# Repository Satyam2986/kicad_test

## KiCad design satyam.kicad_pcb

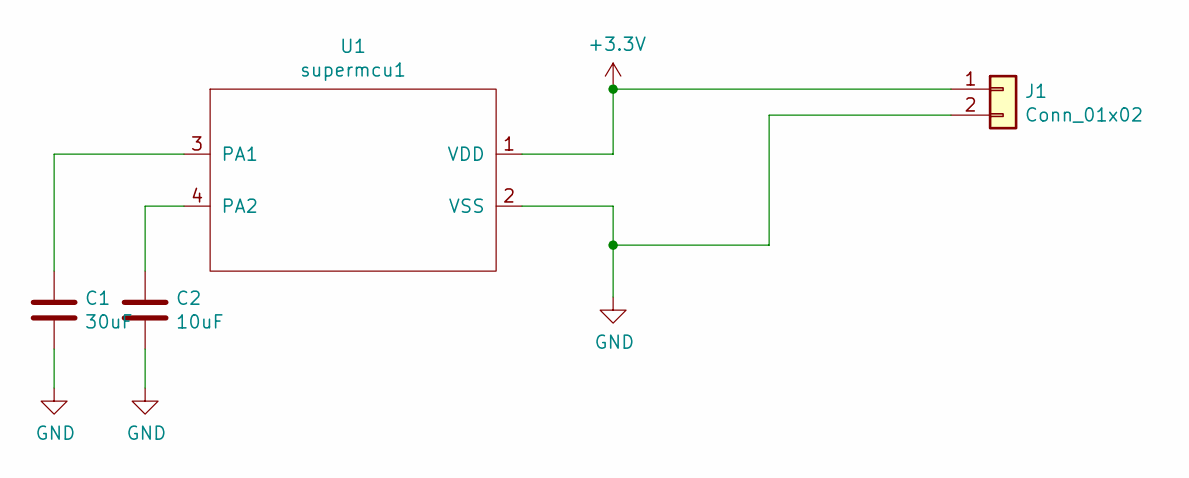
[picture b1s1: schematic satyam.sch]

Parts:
C1: 30uF; C_0805_2012Metric
C2: 10uF; C_0805_2012Metric
J1: Conn_01x02; JST_EH_B2B-EH-A_1x02_P2.50mm_Vertical
U1: supermcu1; SO-4_4.4x2.3mm_P1.27mm

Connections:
+3V3: J1.1, U1.1 (VDD)
GND: C1.2, C2.2, J1.2, U1.2 (VSS)
unnamed: C1.1, U1.3 (PA1)
unnamed: C2.1, U1.4 (PA2)

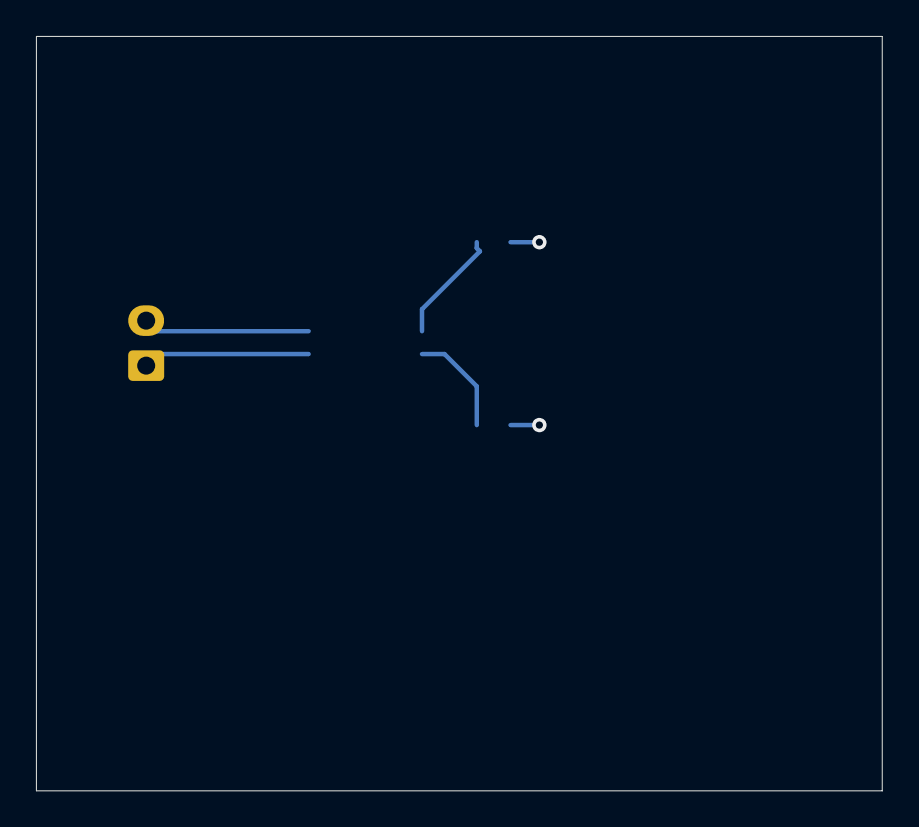
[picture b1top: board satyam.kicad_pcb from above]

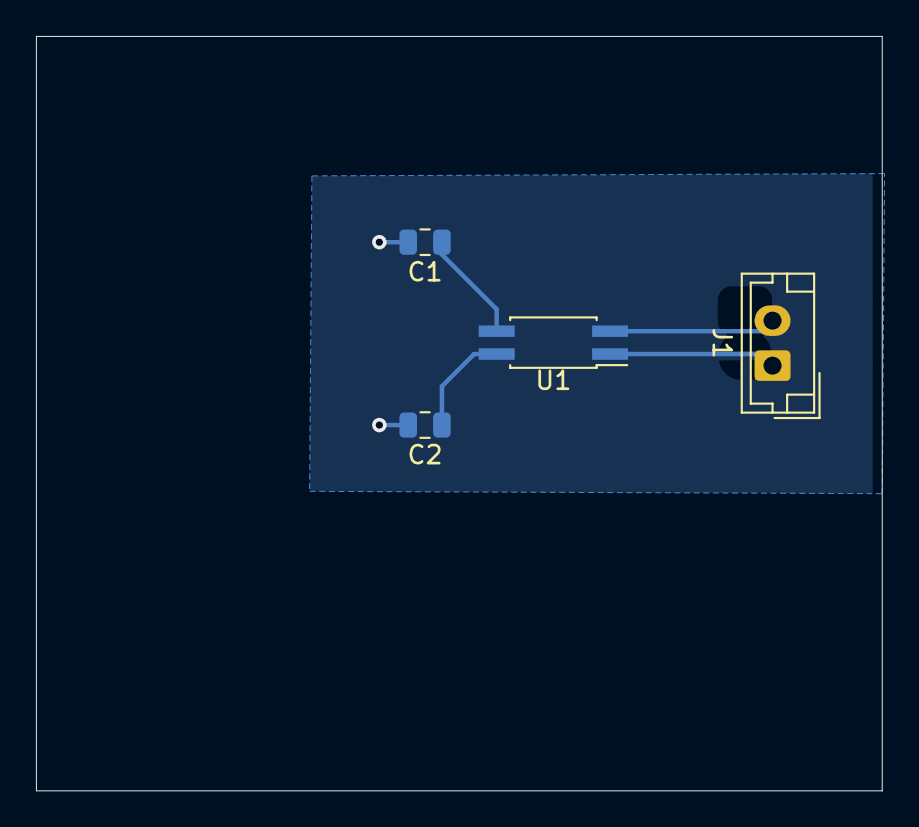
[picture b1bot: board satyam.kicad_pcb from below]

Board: 2 copper layers, 47.0 x 41.9 mm, 4 parts (4 on the bottom side), 4 nets.

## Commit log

2021-06-14 first version
2021-06-14 Change C1 to 30uF
2021-07-05 PCB Layout
2021-07-05 Improved PCB Layout
2021-07-06 Components shifted to bottom
